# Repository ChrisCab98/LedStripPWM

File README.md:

# LedStripPWM
ESP12-E PWM for dimming LED Strip

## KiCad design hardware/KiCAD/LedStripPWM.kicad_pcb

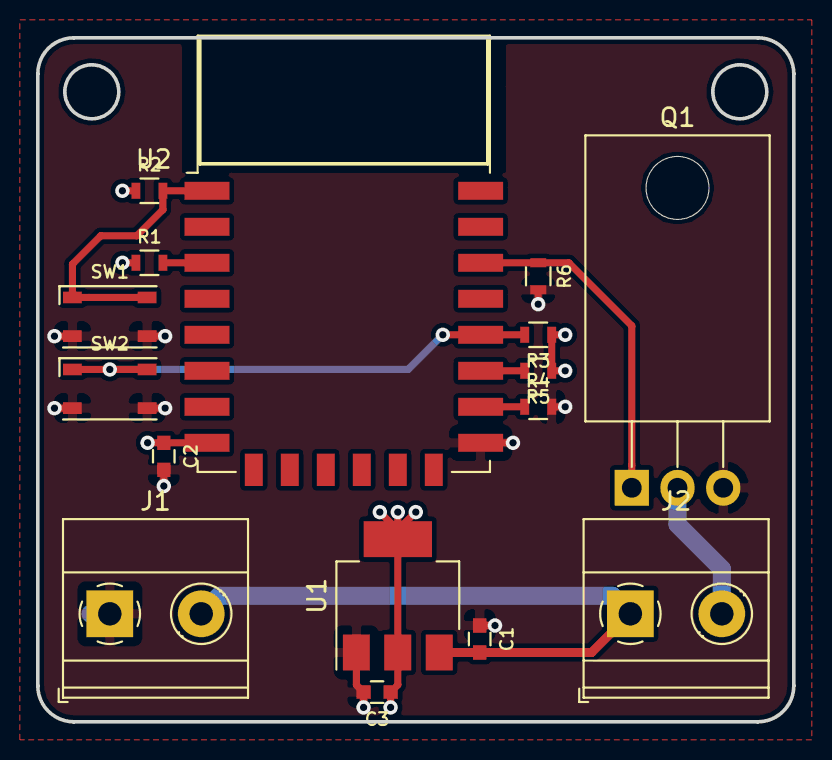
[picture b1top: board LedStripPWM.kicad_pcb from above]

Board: 4 copper layers, 42.0 x 38.0 mm, 16 parts (0 on the bottom side), 10 nets.

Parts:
C1, C3: C_0003; C_0603
C2: C_0029; C_0603
J1, J2: Screw_Terminal_01x02; TerminalBlock_Phoenix_MKDS-1,5-2-5.08_1x02_P5.08mm_Horizont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
Q1: IRLZ44N; TO-220-3_Horizontal_TabDown
R1, R2, R3, R4, R5, R6: R_0065; R_0603
SW1, SW2: SW_0003; PTS810
U1: AZ1117-3.3; SOT-223-3_TabPin2
U2: ESP-12E

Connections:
+3.3V: C2.1, C3.1, R1.1, R2.1, R3.1, R5.1, U1.2, U2.8
+12V: C1.2, J1.2, J2.1, U1.3
/EN: R1.2, U2.3
/GPIO0: R3.2, SW2.1, SW2.2, U2.18
/PWM: Q1.1, R6.1, U2.20
/~RST: R2.2, SW1.1, SW1.2, U2.1
GND: C1.1, C2.2, C3.2, J1.1, Q1.3, R4.2, R6.2, SW1.3, SW1.4, SW2.3, SW2.4, U1.1, U2.15
unnamed: J2.2, Q1.2
unnamed: R4.1, U2.16
unnamed: R5.2, U2.17

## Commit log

2019-09-01 .sch ok / PCB OK
